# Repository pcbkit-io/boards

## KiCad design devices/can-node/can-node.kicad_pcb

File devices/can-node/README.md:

# can-node — an STM32G431 sensor node on a robot's CAN bus

A node for a robot or a machine: four 0–5 V pressure sensors and a 6-axis IMU, sent at 100 Hz as CAN
frames at 500 kbit/s. The bus and the robot's 12 V come in on one JST GH connector; the board
protects itself (reverse polarity, transients) and makes its own 3.3 V. A jumper puts the 120 Ω
terminator on the bus for the two nodes at its ends. Firmware is ST's HAL, flashed over SWD.

| | |
|---|---|
| Processor | STM32G431CBU6 (UFQFPN-48): Arm Cortex-M4F at 170 MHz (8 MHz crystal, PLL, boost mode), FDCAN1 |
| CAN | SN65HVD230 transceiver on PA12 (TX) / PA11 (RX), 500 kbit/s; SD24C TVS on CANH and CANL; 120 Ω terminator through jumper J2 |
| Inputs | J5 (2 × 4, 2.54 mm): four 0–5 V inputs, each with its ground, through an 11 k / 20 k divider and a 1 kHz filter into ADC1 IN1–IN4 (PA0–PA3), sampled by TIM6 at 100 Hz through DMA |
| IMU | ICM-42688-P at 0x68 on I2C1 (PA15 SCL, PB7 SDA) at 400 kHz, ±4 g and ±1000 °/s |
| Power | J1 (JST GH 4-pin: 12 V, CANH, CANL, GND) → AO3401A reverse-polarity P-FET → SMBJ18A TVS → TPS54331 buck → 3.3 V |
| Debug | J4: SWD (3.3 V, SWDIO, SWCLK, NRST, GND) for an ST-LINK; J3: the console (USART1 TX, RX, GND at 115200 baud) for a 3.3 V USB-serial cable; D1: status LED on PB0 |
| Board | 60 × 40 mm, 2 layers, two M3 holes |

Frames it sends (little-endian 16-bit values):

| ID | Data |
|---|---|
| 0x100 | the four inputs in mV at the connector (0–5000) |
| 0x101 | acceleration X, Y, Z in mg, the IMU's temperature in 0.01 °C |
| 0x102 | rotation X, Y, Z in 0.1 °/s |

A frame **0x200** with one byte sets the LED: 0 off, 1 on, 2 blinking.

<!-- STATUS -->
**Board status** (measured on the dev host with PCBKit's CLI): `pcbkit check`: complete — 0 errors, 0 warnings, 0 unrouted nets. 68 components, 37 nets, 494 track segments, 53 vias.
`analysis.run { lens: "ready" }`: nothing to fix, 11 to consider (below).
`pcbkit export --format fab` succeeds without `--force`: every assembled line of the BOM has an LCSC code (JLCPCB assembly).
<!-- /STATUS -->

What the readiness check asks to consider, and why it is fine here:

| Finding | Why |
|---|---|
| J2, J3, J4 are not on an edge | the terminator jumper, the console and the SWD header: set once or used on the bench, no cable stays |
| V3 comes in through J4 unprotected | the SWD header's 3.3 V is the programmer's reference, not a supply |
| D1 runs at 0.3 mA | a status LED; 1 kΩ keeps it from lighting the robot's inside |
| No test points | the console and SWD reach every signal that matters |
| U4 needs an operating load / thermal parameters / family estimates | the analysis' own caveats: the node draws about 120 mA |

## Run it in the browser

Open https://app.pcbkit.io/github/pcbkit-io/boards/tree/main/devices/can-node, open the Laboratory and
press **Build & run**: the page builds `firmware/` with ST's HAL for the STM32G431 and runs it on a
model of the chip. `sim/robot.js` is the robot around it: the gripper's two cylinders filling and
venting (supply pressure, cycle time, a leak on cylinder B, a bump of the robot are controls),
driving the four inputs and the IMU. What you see:

- **CAN_BUS1** — the bus beyond the connector as a USB-CAN adapter: every frame as an SLCAN line
  (`t1008…`); send `t2001` + `02` + CR to make the LED blink.
- **J3** — the console: `can-node 170000000 Hz`, `imu ICM-42688-P`, the inputs once a second.

The model refuses what silicon would not do (a peripheral with its clock off, a PLL outside its
limits) and says so; it does not model the bus's analog waveform or arbitration with other nodes.

## Order, flash, use

1. Order with assembly (JLCPCB: `pcbkit export --format fab`, or `fab.order` in the app).
2. Flash over SWD with an ST-LINK on J4: `pcbkit export --format firmware` gives `U1.bin` and
   `U1.hex`; `st-flash write U1.bin 0x08000000` or STM32CubeProgrammer.
3. Wire J1 to the robot's bus (12 V, CANH, CANL, GND); fit J2's shunt on the two end nodes only.

Licence: CC0 1.0.

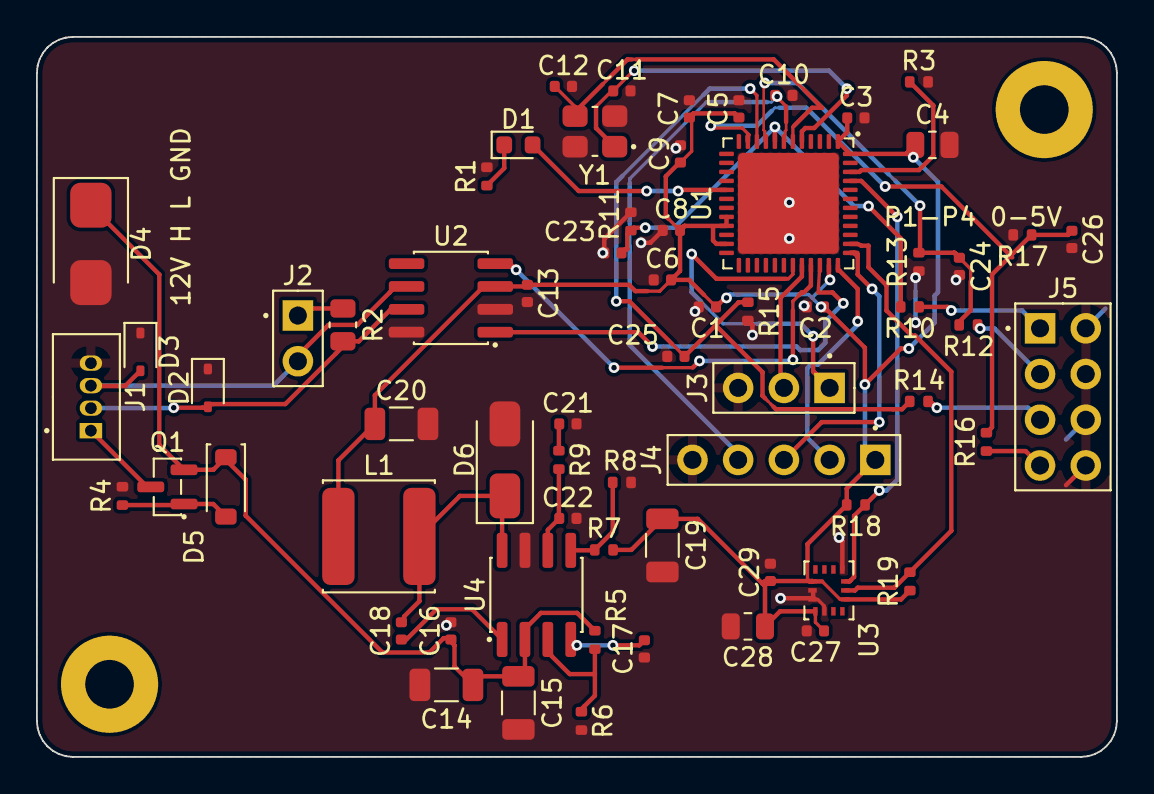
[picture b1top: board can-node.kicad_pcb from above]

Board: 2 copper layers, 60.0 x 40.0 mm, 68 parts (0 on the bottom side), 37 nets.

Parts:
C1, C2, C3, C5, C8, C10, C13, C18, C27: 100nF; C_0402_1005Metric
C4: 4.7uF; C_0805_2012Metric
C6, C16, C17, C29: 10nF; C_0402_1005Metric
C7, C9: 1uF; C_0402_1005Metric
C11, C12: 15pF; C_0402_1005Metric
C14, C15: 4.7uF; C_1206_3216Metric
C19, C20: 47uF; C_1206_3216Metric
C21: 1nF; C_0402_1005Metric
C22: 47pF; C_0402_1005Metric
C23, C24, C25, C26: 22nF; C_0402_1005Metric
C28: 2.2uF; C_0805_2012Metric
D1: green; LED_0603_1608Metric
D2, D3: tvs 24V bidir; D_SOD-323
D4: tvs 18V; D_SMB
D5: zener 5.6V; D_SOD-123
D6: schottky; D_SMA
H1, H2: MountingHole_2.7mm_M2.5_Pad
J1: SM04B-GHS-TB; Conn_WireToBoard_1x04_P1.25mm_THT_Vertical
J2: PinHeader_1x02_P2.54mm_Vertical
J3: PinHeader_1x03_P2.54mm_Vertical
J4: PinHeader_1x05_P2.54mm_Vertical
J5: PinHeader_2x04_P2.54mm_Vertical
L1: 6.8uH; L_Power_6x6mm
Q1: AO3401A; SOT-23
R1: 1kohm; R_0402_1005Metric
R2: 120ohm; R_0805_2012Metric
R3, R18, R19: 10kohm; R_0402_1005Metric
R4: 100kohm; R_0402_1005Metric
R5: 332kohm; R_0402_1005Metric
R6: 68.1kohm; R_0402_1005Metric
R7: 10.2kohm; R_0402_1005Metric
R8: 3.24kohm; R_0402_1005Metric
R9: 29.4kohm; R_0402_1005Metric
R10, R12, R14, R16: 11kohm; R_0402_1005Metric
R11, R13, R15, R17: 20kohm; R_0402_1005Metric
U1: STM32G431CBU6; QFN-48-1EP_7x7mm_P0.5mm_EP5.6x5.6mm
U2: SN65HVD230DR; SOIC-8_3.895x4.905mm_P1.27mm
U3: ICM-42688-P; LGA-14_2.5x3.0x0.91mm_0.5mm_pitch
U4: TPS54331D; SOIC-8_3.9x4.9mm_P1.27mm
Y1: 8MHz 10pF; Crystal_SMD_3225-4Pin

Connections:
A1: C23.1 (a), R10.2 (b), R11.1 (a), U1.8 (PA0)
A2: C24.1 (a), R12.2 (b), R13.1 (a), U1.9 (PA1)
A3: C25.1 (a), R14.1 (a), R15.1 (a), U1.10 (PA2)
A4: C26.1 (a), R16.2 (b), R17.1 (a), U1.11 (PA3)
CANH: D2.2 (A), J1.2, R2.2 (b), U2.7 (CANH)
CANL: D3.2 (A), J1.3, J2.2, U2.6 (CANL)
CAN_RX: U1.33 (PA11), U2.4 (R)
CAN_TX: U1.34 (PA12), U2.1 (D)
GND: C1.2 (b), C2.2 (b), C3.2 (b), C4.2 (b), C5.2 (b), C6.2 (b), C7.2 (b), C8.2 (b), C9.2 (b), C10.2 (b), C11.2 (b), C12.2 (b), C13.2 (b), C14.2 (b), C15.2 (b), C16.2 (b), C17.2 (b), C19.2 (b), C20.2 (b), C21.2 (b), C22.2 (b), C23.2 (b), C24.2 (b), C25.2 (b), C26.2 (b), C27.2 (b), C28.2 (b), C29.2 (b), D2.1 (K), D3.1 (K), D4.2 (A), D6.2 (A), J1.4, J3.3, J4.5, J5.2, J5.4, J5.6, J5.8, R1.2 (b), R3.2 (b), R4.2 (b), R6.2 (b), R8.2 (b), R11.2 (b), R13.2 (b), R15.2 (b), R17.2 (b), U1.49 (VSS), U2.2 (GND), U2.8 (RS), U3.1 (AP_AD0), U3.6 (GND), U3.7 (RESV7), U3.9 (INT2), U4.7 (GND), Y1.2 (GND), Y1.4 (GND)
LED: D1.2 (A), U1.17 (PB0)
LED_K: D1.1 (K), R1.1 (a)
NRST: C10.1 (a), J4.4, U1.7 (PG10)
unnamed: C17.1 (a), U4.4 (SS)
unnamed: C18.1 (a), U4.1 (BOOT)
unnamed: C18.2 (b), D6.1 (K), L1.2 (b), U4.8 (PH)
unnamed: C22.1 (a), R9.2 (b), U4.6 (COMP)
unnamed: R3.1 (a), U1.46 (PB8)
unnamed: R5.2 (b), R6.1 (a), U4.3 (EN)
unnamed: R7.2 (b), R8.1 (a), U4.5 (VSENSE)
P1: J5.1, R10.1 (a)
P2: J5.3, R12.1 (a)
P3: J5.5, R14.2 (b)
P4: J5.7, R16.1 (a)
RX: J3.2, U1.32 (PA10)
SCL: R19.1 (a), U1.38 (PA15), U3.13 (AP_SCL)
SDA: R18.1 (a), U1.45 (PB7), U3.14 (AP_SDA)
SWCLK: J4.3, U1.37 (PA14)
SWDIO: J4.2, U1.36 (PA13)
TERM: J2.1, R2.1 (a)
TX: J3.1, U1.31 (PA9)
U4Support/COMP_RC: C21.1 (a), R9.1 (a)
V3: C1.1 (a), C2.1 (a), C3.1 (a), C4.1 (a), C5.1 (a), C6.1 (a), C7.1 (a), C8.1 (a), C9.1 (a), C13.1 (a), C19.1 (a), C20.1 (a), C27.1 (a), C28.1 (a), C29.1 (a), J4.1, L1.1 (a), R7.1 (a), R18.2 (b), R19.2 (b), U1.1 (VBAT), U1.20 (VREFP), U1.21 (VDDA), U1.23 (VDD), U1.35 (VDD), U1.48 (VDD), U2.3 (VCC), U3.5 (VDDIO), U3.8 (VDD), U3.12 (AP_CS)
V12: C14.1 (a), C15.1 (a), C16.1 (a), D4.1 (K), D5.1 (K), Q1.2 (S), R5.1 (a), U4.2 (VIN)
VIN: J1.1, Q1.3 (D)
XIN: C11.1 (a), U1.5 (PF0), Y1.1 (X1)
XOUT: C12.1 (a), U1.6 (PF1), Y1.3 (X2)
reversed/gate: D5.2 (A), Q1.1 (G), R4.1 (a)

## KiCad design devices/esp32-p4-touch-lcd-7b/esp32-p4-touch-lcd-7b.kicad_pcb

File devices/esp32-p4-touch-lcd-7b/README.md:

# esp32-p4-touch-lcd-7b — Waveshare's ESP32-P4 7" touch board, running PocketJS

Waveshare's [ESP32-P4-WIFI6-Touch-LCD-7B](https://www.waveshare.com/wiki/ESP32-P4-WIFI6-Touch-LCD-7B)
as a PCBKit project: its circuit read from Waveshare's published schematic, its parts where
Waveshare's assembly drawing puts them (the connectors on the same edges, the chips in the same
places), behind the same 7" 1024 × 600 panel. In the app it runs
[PocketJS](https://github.com/pocket-nexus/pocketjs)'s ESP32-P4 host for this board (pull
request #208, MIT) with its stock Feature Cards app: one flash image, published by PCBKit as a
[release of this repository](https://github.com/pcbkit-io/boards/releases/tag/pocketjs-esp32p4-7b-5d4a16b9),
booted by Espressif's ESP32-P4 boot ROM on PCBKit's model of the chip.

| | |
|---|---|
| Processor | ESP32-P4NRW32 (two RISC-V cores at 360 MHz, 32 MB PSRAM in package), GD25Q256 32 MB flash, 40 MHz and 32.768 kHz crystals, a CR1220 for its clock |
| Screen | 7" 1024 × 600 IPS, EK79007 over 2-lane MIPI-DSI (P2, 30 pins), GT911 touch on I2C (J3, 6 pins, GPIO7/8, INT GPIO23); AVDD 9.6 V from an AP3012, VGH and VGL from charge pumps, the backlight from an AP3032 dimmed by GPIO32 |
| Sound | ES8311 codec, NS4150B 3 W amplifier (GPIO53) to the speaker (H7); ES7210 four-channel ADC with two ZTS6117 microphones and the speaker's own signal for echo cancelling; I2S on GPIO9–13 |
| Radio | ESP32-C6-MINI-1 on the P4's second SD/MMC slot (GPIO14–19), its antenna at the top edge |
| Storage | microSD on SD/MMC slot 0 (GPIO39–44), its supply switched by GPIO45 |
| Camera | 15-pin 1 mm MIPI-CSI connector (J2), Raspberry Pi's pinout |
| Ports | RS-485 (SP3485, automatic direction), CAN (TJA1051T/3), I2C through an NDC7002N level shifter, the console's UART, two 12-pin headers of GPIOs (PH2.0) |
| USB | USB-C console (CH343P, automatic boot), USB-C to the P4's full-speed USB, USB-A host (1 A switch) |
| Power | the two USB-C ORed by ideal diodes, a Li-ion cell (IP5306 charger and boost), a slide switch, SY8089 bucks to 3.3 V and to the P4's 1.2 V |
| Board | 165.5 × 98 mm, 6 layers (JLCPCB JLC06161H-3313), four M2.5 holes |

Parts Waveshare uses that JLCPCB did not stock (2026-10-25), each replaced by one doing the same
job: the MP1658 and MP1605 bucks by SY8089s, the DIO7003 load switch by an SY6280, the ETA6098
charger and SCT12A0 boost by an IP5306, the EMH4 dual transistor by two MMBT3904s, the THVD1406 by
an SP3485. The RS-485 gas discharge tube and the 120 Ω termination jumpers are left out.

<!-- STATUS -->
**Board status** (measured on the dev host with PCBKit's CLI): `pcbkit check`: complete — 0 errors,
47 warnings (the DSI, CSI and USB pairs' coupling and skew: the router lays each pair as two
tracks; 26 tracks narrowed to 0.09 mm between the P4's pins; one 3.3 V track's current), 0
unrouted nets. 293 components, 206 nets, 3993 track segments, 852 vias.
`analysis.run { lens: "ready" }`: 17 to fix — the FPC connectors (P2, J3, J2) inside the board, as
the panel's tails and the camera's ribbon reach them from behind; decoupling 3–6 mm from some P4
pins (its 0402s on the back) and 10–14 mm from the C6 and the IP5306; the analysis's estimate of
ground's heating (it gives each ground stub to the plane the board's whole current).
Every assembled line has its LCSC code (110, chosen by stock at JLCPCB, 2026-10-25); `pcbkit export
--format fab` succeeds without `--force`. **JLCPCB has no ESP32-P4 in stock**: send it as a
consigned part.
<!-- /STATUS -->

## Run it in the browser

Open the board and press **Run**: the page fetches the PocketJS image (checked against the
SHA-256 this design declares) and Espressif's ROM, and runs them. Feature Cards comes up in
about seven seconds; tap a card on the screen in 3D and it opens its details. The same release has
PocketJS's Music ("Now Playing") and Chrome apps for this host: put one of their URLs, SHA-256s
and sizes into the processor's `image` to run it instead. The console (H8) shows PocketJS's
log.

What does not run here, and says so:

- **No radio.** The ESP32-C6 is on the board but held in reset: its firmware (ESP-Hosted) does
  not run, so there is no Wi-Fi or Bluetooth. Nothing pretends to be a network.
- **CAN.** PCBKit's ESP32-P4 model has no TWAI controller yet: the TJA1051 stays unconnected
  (the laboratory lists it among its limitations).
- The ES7210 (the microphones), the camera and the RS-485 transceiver have no models yet.

## Order, flash

1. Order with assembly (`pcbkit export --format fab`); the panel plugs into P2 and J3. JLCPCB has
   no ESP32-P4 in stock: send it as a consigned part.
2. Flash over the console's USB-C: `esptool.py --chip esp32p4 write_flash 0
   pocketjs-esp32p4-waveshare-7b-cards-factory.bin` (the CH343P's DTR and RTS put the P4 into
   its boot loader).

Licence: the board CC0 1.0; Waveshare's schematic is its own, read for the circuit (no files of
it here); PocketJS MIT, fetched from the release and never copied into the project.

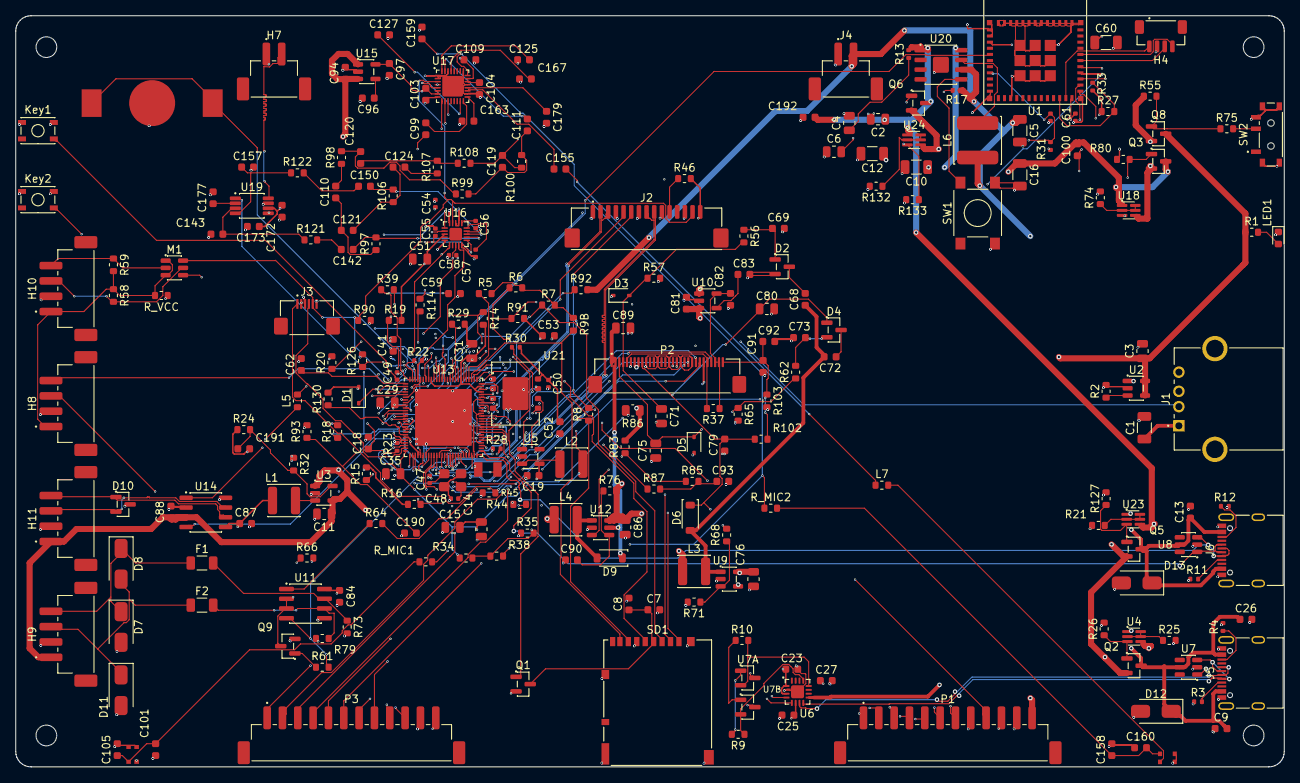
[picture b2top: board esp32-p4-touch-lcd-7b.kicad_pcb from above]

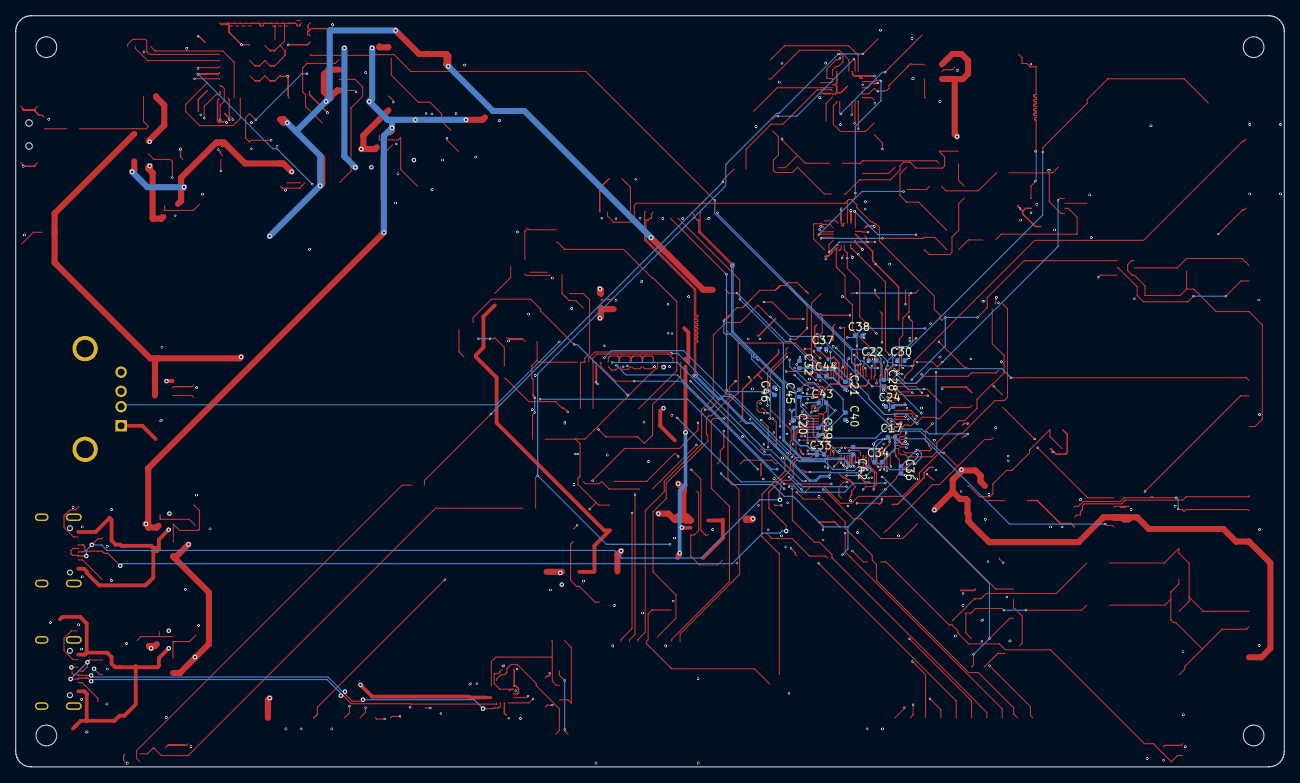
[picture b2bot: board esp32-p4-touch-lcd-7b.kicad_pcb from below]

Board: 6 copper layers, 165.5 x 98.0 mm, 293 parts (21 on the bottom side), 203 nets.

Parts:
BAT1: KH-CR1220-2; BatteryHolder_CR1220_SMD
C1: 100uF; C_1206_3216Metric
C2, C3, C4, C6, C29, C31, C35, C51, C71, C75, C76, C80, C86: 10uF; C_0805_2012Metric
C5, C10, C12, C16, C60: 22uF; C_1206_3216Metric
C7, C18, C19, C52, C92, C94, C97, C172: 10uF; C_0603_1608Metric
C8, C26, C27, C53, C68, C72, C79, C84, C87, C88, C91, C93, C103, C104, C105, C142, C150, C160, C173, C190: 100nF; C_0603_1608Metric
C9, C13, C23, C25, C41, C69, C73, C81, C82, C90, C99, C100, C109, C127, C155, C159, C163, C167, C177, C179, C192: 1uF; C_0603_1608Metric
C11, C14, C15: 22uF; C_0805_2012Metric
C17, C20, C21, C22, C24, C28, C30, C32, C33, C34, C36, C37, C38, C39, C40, C42, C50, C54, C61: 100nF; C_0402_1005Metric
C43, C44, C45, C46, C49, C55, C56, C57, C58, C63: 1uF; C_0402_1005Metric
C47, C48: 15pF; C_0402_1005Metric
C59, C62, C143, C157, C191: 22pF; C_0603_1608Metric
C83, C96: 22nF; C_0603_1608Metric
C89: 1uF; C_0805_2012Metric
C101, C158: 2.2uF; C_0603_1608Metric
C110, C124: 470nF; C_0603_1608Metric
C111, C125: 220nF; C_0603_1608Metric
C119: 100pF; C_0603_1608Metric
C120: 2.2nF; C_0603_1608Metric
C121: 10nF; C_0603_1608Metric
D1: schottky; D_SOD-323
D2, D4: BAT54S-7-F; SOT-23
D3: zener 7.5V; D_SOD-323
D5: zener 18V; D_SOD-323
D6, D9: schottky; D_SOD-123
D7, D8, D11: tvs 12V bidir; D_SMA
D10: SM24CANB-02HTG; SOT-23
D12, D13: tvs 5V; D_SMA
F1, F2: PTC 200mA; Fuse_1206_3216Metric
H4: SH1.0-4P SMD vertical; Conn_WireToBoard_1x04_P1.00mm_SMD_Vertical
H7: PH2.0-2P SMD vertical; Conn_WireToBoard_1x02_P2.00mm_SMD_Vertical
H8, H9, H10, H11: PH2.0-4P SMD vertical; Conn_WireToBoard_1x04_P2.00mm_SMD_Vertical
J1: USB-A 90deg; USB_A_Receptacle_THT_Horizontal
J2: FPC 1.0mm 15P flip-lock bottom contact; Conn_FFC-FPC_1x15_P1.00mm_Horizontal
J3: FPC 0.5mm 6P flip-lock top contact; Conn_FFC-FPC_1x06_P0.50mm_Horizontal
J4: PH2.0-2P SMD vertical; Conn_WireToBoard_1x02_P2.00mm_SMD_Vertical
J5, J6: USB4105-GF-A; USB_C_Receptacle_USB2.0_16P
Key1, Key2: PTS810SJM250SMTR LFS; SW_Tactile_SPST_4.2x3.2mm_SMD
L1, L2: 2.2uH; L_Power_4x4mm
L3, L4: 10uH; L_Power_4x4mm
L5, L7: 0uohm; R_0603_1608Metric
L6: 1uH; L_Power_6x6mm
LCD1: touch-display; Waveshare-7inch-1024x600-DSI
LED1: red; LED_0603_1608Metric
LSK1, LSK2, LSK3, LSK4: MountingHole_2.7mm_M2.5
M1: NDC7002N; SOT-23-6
MIC1, MIC2: ZTS6117; MEMS_Mic_ZTS6117_2.75x1.85mm
P1, P3: PH2.0-12P SMD vertical; Conn_WireToBoard_1x12_P2.00mm_SMD_Vertical
P2: FPC 0.5mm 30P flip-lock bottom contact; Conn_FFC-FPC_1x30_P0.50mm_Horizontal
Q1, Q2, Q3, Q5, Q6, Q8: AO3401A; SOT-23
Q9: MMBT3904-7-F; SOT-23
R1: 7.5kohm; R_0603_1608Metric
R2: 6.8kohm; R_0603_1608Metric
R3, R4, R11, R12: 5.1kohm; R_0402_1005Metric
R5, R6, R7, R8, R9, R9B, R10, R14, R21, R25, R27, R29, R37, R45, R46, R73, R74, R75, R79, R87, R98, R107, R126, R132: 10kohm; R_0603_1608Metric
R13, R17: 2ohm; R_0402_1005Metric
R15, R16, R18, R19, R20, R26, R57, R65, R80, R127, R130, R133: 51kohm; R_0603_1608Metric
R22, R30, R31, R33: 10kohm; R_0402_1005Metric
R23, R28: 2kohm; R_0402_1005Metric
R24: 453kohm; R_0603_1608Metric
R32, R76, R93: 100kohm; R_0603_1608Metric
R34, R35: 499kohm; R_0603_1608Metric
R38: 0uohm; R_0603_1608Metric
R39: 10Mohm; R_0603_1608Metric
R44, R58, R59, R61, R64, R66: 4.7kohm; R_0603_1608Metric
R55: 110kohm; R_0603_1608Metric
R56, R62: 220ohm; R_0603_1608Metric
R68: 22kohm; R_0603_1608Metric
R71: 3.3kohm; R_0603_1608Metric
R83: 5.1kohm; R_0603_1608Metric
R85: 68kohm; R_0603_1608Metric
R86: 1.3ohm; R_0805_2012Metric
R90, R91, R97, R106: 2.2kohm; R_0603_1608Metric
R92: 200kohm; R_0603_1608Metric
R99, R108: 20kohm; R_0603_1608Metric
R100: 4.3kohm; R_0603_1608Metric
R102: 2kohm; R_0603_1608Metric
R103: 1kohm; R_0603_1608Metric
R114: 51ohm; R_0603_1608Metric
R121, R122: 150kohm; R_0603_1608Metric
R_MIC1, R_MIC2: 0uohm; R_0603_1608Metric
R_VCC: 0uohm; R_0603_1608Metric
SD1: DM3AT-SF-PEJM5; Hirose_DM3AT_microSD_socket_push-push
SW1: PTS645SM43SMTR92 LFS; SW_Tactile_SPST_6x6mm_SMD
SW2: MSK12C02; SW_Slide_SPDT_Shouhan_MSK12C02
U1: ESP32-C6-MINI-1-N4; ESP32-C6-MINI-1_module_13.2x16.6mm_LGA_53_pads
U2: SY6280AAC; SOT-23-5
U3, U5: SY8089AAAC; SOT-23-5
U4, U18, U23, U24: MMDT3906DW; SOT-363
U6: CH343P; QFN-16-1EP_3x3mm_P0.5mm_EP1.7x1.7mm
U7, U8: USBLC6-2SC6; SOT-23-6
U7A, U7B: MMBT3904-7-F; SOT-23
U9: AP3012KTR-E1; SOT-23-5
U10: RT9193-18GB; SOT-23-5
U11: SP3485EN-L/TR; SOIC-8_3.9x4.9mm_P1.27mm
U12: AP3032KTR-G1; SOT-23-6
U13: ESP32-P4NRW32; QFN-104_10x10mm_0.35mm_pitch_7.5mm_exposed_pad
U14: TJA1051T/3/1J; SOIC-8_3.9x4.9mm_P1.27mm
U15: RT9193-33GB; SOT-23-5
U16: ES8311; QFN-20-1EP_3x3mm_P0.4mm_EP1.65x1.65mm
U17: ES7210; QFN-32-1EP_4x4mm_P0.4mm_EP2.7x2.7mm
U19: NS4150B; MSOP-8_3x3mm_P0.65mm
U20: IP5306; SOIC-8-1EP_3.9x4.9mm_P1.27mm_EP2.09x2.09mm
U21: GD25Q256EYIGR; DFN-8-1EP_6x8mm_P1.27mm_EP3.4x4.3mm
Y1: 40MHz 10pF; Crystal_SMD_3225-4Pin
Y3: Q13FC13500004; Crystal_SMD_3215-2Pin_3.2x1.5mm

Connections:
A3V3: C55.1 (a), C97.1 (a), C103.1 (a), C104.1 (a), C109.1 (a), U15.5 (VOUT), U16.11 (AVDD), U17.6 (VDDP), U17.7 (VDDD), U17.22 (VDDA), U17.23 (VDDM)
A3V3_BP: C96.1 (a), U15.4 (BP)
ADC_MIC3_N: C125.2 (b), U17.32 (MIC3N)
ADC_MIC3_P: C111.2 (b), U17.31 (MIC3P)
ADC_MICBIAS12: C159.1 (a), R_MIC1.1 (a), R_MIC2.1 (a), U17.24 (MICBIAS12)
AEC_N1: C121.2 (b), C124.1 (a), R106.2 (b)
AEC_N2: C124.2 (b), R107.1 (a)
AEC_N3: C120.2 (b), R107.2 (b), R108.1 (a)
AEC_N4: C119.2 (b), C125.1 (a), R100.2 (b), R108.2 (b)
AEC_P1: C110.1 (a), C121.1 (a), R97.2 (b)
AEC_P2: C110.2 (b), R98.1 (a)
AEC_P3: C120.1 (a), R98.2 (b), R99.1 (a)
AEC_P4: C111.1 (a), C119.1 (a), R99.2 (b), R100.1 (a)
AVDD: C79.1 (a), C80.1 (a), D4.1 (A1), D6.1 (K), P2.9, R68.1 (a), R102.2 (b)
AVDD_FB: R68.2 (b), R71.1 (a), U9.3 (FB)
BAT: C5.1 (a), J4.2, L6.1 (a), P1.12, R17.1 (a), R92.1 (a), U20.6 (BAT)
BAT_SENSE: C190.1 (a), R92.2 (b), R93.1 (a), U13.22 (GPIO20)
BL_CTRL: R87.1 (a), U13.63 (GPIO32)
BL_DIM: C93.1 (a), R85.2 (b), R87.2 (b)
BL_EN: C90.1 (a), R76.1 (a), U12.4 (EN)
BL_FB: R83.2 (b), R85.1 (a), U12.3 (FB)
BL_SW: D9.2 (A), L4.1 (a), U12.1 (SW)
BOOST_5V: C10.1 (a), C12.1 (a), C16.1 (a), C100.1 (a), Q3.3 (D), U18.1 (E2), U20.8 (VOUT)
BOOT: Key2.1 (a), R44.1 (a), U7B.3 (C), U13.66 (GPIO35)
C6_CHIP_PU: C63.1 (a), R31.1 (a), U1.8 (EN), U13.98 (GPIO54)
C6_CLK: R20.1 (a), U1.25 (IO19), U13.19 (GPIO18)
C6_CMD: R130.1 (a), U1.24 (IO18), U13.20 (GPIO19)
C6_D0: R19.1 (a), U1.26 (IO20), U13.15 (GPIO14)
C6_D1: R18.1 (a), U1.27 (IO21), U13.16 (GPIO15)
C6_D2: R16.1 (a), U1.28 (IO22), U13.17 (GPIO16)
C6_D3: R15.1 (a), U1.29 (IO23), U13.18 (GPIO17)
C6_IO2: U1.5 (IO2), U13.6 (GPIO6)
C6_IO8: R27.1 (a), R33.1 (a), U1.22 (IO8)
C6_IO9: H4.1, U1.23 (IO9)
C6_U0RXD: H4.3, U1.30 (RXD0)
C6_U0TXD: H4.4, U1.31 (TXD0)
CANH: D10.2 (H), H11.3, U14.7 (CANH)
CANL: D10.1 (L), H11.4, U14.6 (CANL)
CANRX: U13.23 (GPIO21), U14.4 (RXD)
CANTX: U13.24 (GPIO22), U14.1 (TXD)
CORE_5V: C3.1 (a), C11.1 (a), C76.1 (a), C81.1 (a), C86.1 (a), C88.1 (a), C94.1 (a), H9.1, H11.1, L3.1 (a), L4.2 (b), Q8.3 (D), R1.1 (a), R76.2 (b), U2.4 (EN), U2.5 (IN), U3.1 (EN), U3.4 (IN), U9.4 (SHDN), U9.5 (VIN), U10.1 (VIN), U10.3 (EN), U12.6 (VIN), U14.3 (VCC), U15.1 (VIN), U15.3 (EN)
CSI_CLK_N: J2.8, U13.45 (CSI_CLKN)
CSI_CLK_P: J2.9, U13.44 (CSI_CLKP)
CSI_D0_N: J2.2, U13.42 (CSI_DATAN0)
CSI_D0_P: J2.3, U13.43 (CSI_DATAP0)
CSI_D1_N: J2.5, U13.46 (CSI_DATAN1)
CSI_D1_P: J2.6, U13.47 (CSI_DATAP1)
CSI_IO0: J2.11, R46.1 (a)
DSI_CLK_N: P2.18, U13.37 (DSI_CLKN)
DSI_CLK_P: P2.17, U13.38 (DSI_CLKP)
DSI_D0_N: P2.24, U13.40 (DSI_DATAN0)
DSI_D0_P: P2.23, U13.39 (DSI_DATAP0)
DSI_D1_N: P2.21, U13.36 (DSI_DATAN1)
DSI_D1_P: P2.20, U13.35 (DSI_DATAP1)
DTR: R10.2 (b), U6.12 (DTR#), U7A.2 (E)
D_SCL: H10.4, M1.2 (S2), R59.1 (a)
D_SDA: H10.3, M1.5 (S1), R58.2 (b)
EN_DCDC: U5.1 (EN), U13.79 (EN_DCDC)
ES7210_REFP12: C163.1 (a), U17.17 (REFP12)
ES7210_REFP34: C167.1 (a), U17.29 (REFP34)
ES7210_SDOUT: R114.1 (a), U17.11 (SDOUT1)
ESP_3V3: C14.1 (a), C15.1 (a), C17.1 (a), C19.1 (a), C20.1 (a), C21.1 (a), C22.1 (a), C23.1 (a), C24.1 (a), C25.1 (a), C27.1 (a), C29.1 (a), C30.1 (a), C31.1 (a), C32.1 (a), C33.1 (a), C34.1 (a), C50.1 (a), C51.1 (a), C52.1 (a), C53.1 (a), C54.1 (a), C60.1 (a), C61.1 (a), C84.1 (a), C87.1 (a), C172.1 (a), C173.1 (a), C191.1 (a), D1.2 (A), J2.15, J3.2, L1.2 (b), P1.10, P3.12, Q1.2 (S), R14.2 (b), R15.2 (b), R16.2 (b), R18.2 (b), R19.2 (b), R20.2 (b), R22.2 (b), R24.1 (a), R27.2 (b), R30.2 (b), R31.2 (b), R33.2 (b), R44.2 (b), R46.2 (b), R66.2 (b), R79.2 (b), R90.2 (b), R91.2 (b), R130.2 (b), R_VCC.1 (a), U1.3 (P3V3), U5.4 (IN), U6.1 (VIO), U6.3 (VDD5), U6.6 (V3), U11.8 (VCC), U13.9 (VDD_LP), U13.21 (VDD_IO_0), U13.30 (VDD_FLASHIO), U13.51 (VDD_USBPHY), U13.62 (VDD_IO_4), U13.75 (VDD_LDO), U13.77 (VDD_DCDCC), U13.85 (VDD_IO_5), U13.96 (VDD_IO_6), U13.101 (VDD_ANA), U14.5 (VIO), U16.3 (PVDD), U16.4 (DVDD), U19.6 (VDD), U21.8 (VCC)
ESP_EN: C49.1 (a), Key1.1 (a), R22.1 (a), U7A.3 (C), U13.103 (CHIP_PU)
ESP_I2C_SCL: J2.13, J3.6, M1.4 (D2), R91.1 (a), U13.8 (GPIO8), U16.1 (CCLK), U17.4 (CCLK)
ESP_I2C_SDA: J2.14, J3.5, M1.6 (D1), R90.1 (a), U13.7 (GPIO7), U16.19 (CDATA), U17.3 (CDATA)
ESP_LDO_VO4: C46.1 (a), P1.9, R5.2 (b), R6.2 (b), R7.2 (b), R8.1 (a), R9B.1 (a), U13.74 (VDDO_4)
ESP_VBAT: BAT1.1 (+), C28.1 (a), C41.1 (a), D1.1 (K), U13.102 (VDD_BAT)
ESP_VDD_HP: C18.1 (a), C35.1 (a), C36.1 (a), C37.1 (a), C38.1 (a), L2.1 (a), R34.2 (b), U13.26 (VDD_HP_0), U13.76 (VDD_HP_2), U13.91 (VDD_HP_3)
FB_DCDC: R38.1 (a), U13.78 (FB_DCDC)
GND: BAT1.2 (-), C1.2 (b), C2.2 (b), C3.2 (b), C4.2 (b), C5.2 (b), C6.2 (b), C7.2 (b), C8.2 (b), C9.2 (b), C10.2 (b), C11.2 (b), C12.2 (b), C13.2 (b), C14.2 (b), C15.2 (b), C16.2 (b), C17.2 (b), C18.2 (b), C19.2 (b), C20.2 (b), C21.2 (b), C22.2 (b), C23.2 (b), C24.2 (b), C25.2 (b), C26.2 (b), C27.2 (b), C28.2 (b), C29.2 (b), C30.2 (b), C31.2 (b), C32.2 (b), C33.2 (b), C34.2 (b), C35.2 (b), C36.2 (b), C37.2 (b), C38.2 (b), C39.2 (b), C40.2 (b), C41.2 (b), C42.2 (b), C43.2 (b), C44.2 (b), C45.2 (b), C46.2 (b), C47.2 (b), C48.2 (b), C49.2 (b), C50.2 (b), C51.2 (b), C52.2 (b), C53.2 (b), C54.2 (b), C55.2 (b), C56.2 (b), C57.2 (b), C58.2 (b), C59.2 (b), C60.2 (b), C61.2 (b), C62.2 (b), C63.2 (b), C69.2 (b), C71.2 (b), C73.2 (b), C75.2 (b), C76.2 (b), C79.2 (b), C80.2 (b), C81.2 (b), C82.2 (b), C83.2 (b), C84.2 (b), C86.2 (b), C87.2 (b), C88.2 (b), C89.2 (b), C90.2 (b), C91.2 (b), C92.2 (b), C93.2 (b), C94.2 (b), C96.2 (b), C97.2 (b), C100.2 (b), C101.2 (b), C103.2 (b), C104.2 (b), C105.2 (b), C109.2 (b), C127.2 (b), C143.2 (b), C157.2 (b), C158.2 (b), C159.2 (b), C160.2 (b), C163.2 (b), C167.2 (b), C172.2 (b), C173.2 (b), C177.2 (b), C179.2 (b), C190.2 (b), C192.2 (b), D2.2 (K2), D3.1 (K), D5.2 (A), D7.2 (A), D10.3 (GND), D11.2 (A), D12.2 (A), D13.2 (A), H4.2, H8.2, H9.2, H10.2, H11.2, J1.4 (GND), J2.1, J2.4, J2.7, J2.10, J3.3, J4.1, J5.A1 (GND), J5.A12, J5.B1 (GND), J5.B12, J5.S1 (SHIELD), J6.A1 (GND), J6.A12, J6.B1 (GND), J6.B12, J6.S1 (SHIELD), Key1.2 (b), Key2.2 (b), LED1.1 (K), MIC1.2 (GND), MIC1.3 (GND), MIC2.2 (GND), MIC2.3 (GND), P1.8, P1.11, P2.6, P2.10, P2.13, P2.16, P2.19, P2.22, P2.25, P3.11, Q9.2 (E), R2.2 (b), R3.2 (b), R4.2 (b), R11.2 (b), R12.2 (b), R21.2 (b), R23.2 (b), R25.2 (b), R26.2 (b), R28.2 (b), R29.2 (b), R32.2 (b), R35.2 (b), R45.2 (b), R57.2 (b), R65.2 (b), R71.2 (b), R73.2 (b), R74.2 (b), R80.2 (b), R86.2 (b), R93.2 (b), R103.2 (b), R126.2 (b), R127.2 (b), R132.2 (b), R133.2 (b), SD1.6 (VSS), SD1.SH, SW1.2 (b), SW2.3 (B), SW2.4 (SHELL), U1.1 (GND), U1.2 (GND), U1.11 (GND), U1.14 (GND), U1.36 (GND), U1.37 (GND), U1.38 (GND), U1.39 (GND), U1.40 (GND), U1.41 (GND), U1.42 (GND), U1.43 (GND), U1.44 (GND), U1.45 (GND), U1.46 (GND), U1.47 (GND), U1.48 (GND), U1.49 (GND), U1.50 (GND), U1.51 (GND), U1.52 (GND), U1.53 (GND), U2.2 (GND), U3.2 (GND), U5.2 (GND), U6.2 (GND), U6.17 (GND), U7.2 (GND), U8.2 (GND), U9.2 (GND), U10.2 (GND), U11.5 (GND), U12.2 (GND), U13.105 (GND), U14.2 (GND), U14.8 (S), U15.2 (GND), U16.5 (DGND), U16.10 (AGND), U16.17 (MIC1N), U16.18 (MIC1P), U16.20 (CE), U17.1 (AD0), U17.2 (AD1), U17.8 (GNDD), U17.18 (REFQ12), U17.21 (GNDA), U17.25 (REFQM), U17.30 (REFQ34), U17.33 (E_GND), U19.7 (GND), U20.9 (GND), U21.4 (GND), U21.9 (GND), Y1.2 (GND), Y1.4 (GND)
GPIO2: P3.10, U13.2 (GPIO2)
GPIO3: P3.9, U13.3 (GPIO3)
GPIO4: P3.8, U13.4 (GPIO4)
GPIO5: P3.7, U13.5 (GPIO5)
GPIO28: P3.6, U13.57 (GPIO28)
GPIO29: P3.5, U13.58 (GPIO29)
GPIO30: P3.4, U13.60 (GPIO30)
GPIO31: P3.3, U13.61 (GPIO31)
GPIO34: P3.2, U13.65 (GPIO34)
GPIO36: P3.1, R14.1 (a), U13.68 (GPIO36)
GPIO46: P1.7, U13.88 (GPIO46)
GPIO47: P1.6, U13.89 (GPIO47)
GPIO48: P1.5, U13.90 (GPIO48)
GPIO49: P1.4, U13.92 (GPIO49)
GPIO50: P1.3, U13.93 (GPIO50)
GPIO51: P1.2, U13.94 (GPIO51)
GPIO52: P1.1, U13.95 (GPIO52)
H1/power/cc1: J5.A5 (CC1), R3.1 (a)
H1/power/cc2: J5.B5 (CC2), R4.1 (a)
H2/power/cc1: J6.A5 (CC1), R11.1 (a)
H2/power/cc2: J6.B5 (CC2), R12.1 (a)
HP_FB: R34.1 (a), R35.1 (a), R38.2 (b), U5.5 (FB)
I2S_ASDOUT: R114.2 (b), U13.12 (GPIO11)
I2S_DSDIN: U13.10 (GPIO9), U16.9 (DSDIN)
I2S_LRCK: U13.11 (GPIO10), U16.8 (LRCK), U17.10 (LRCK)
I2S_MCLK: U13.14 (GPIO13), U16.2 (MCLK), U17.5 (MCLK)
I2S_SCLK: U13.13 (GPIO12), U16.6 (SCLK), U17.9 (SCLK)
INT_TP: J3.4, U13.25 (GPIO23)
ISET: R2.1 (a), U2.3 (ISET)
KEY: R75.2 (b), SW2.2 (COM)
LCD_STBY: P2.5, P2.26, R37.2 (b)
LCD_SW: C68.1 (a), C72.2 (b), D6.2 (A), L3.2 (b), U9.1 (SW)
LED1_A: LED1.2 (A), R1.2 (b)
LEDN: P2.7, P2.8, R83.1 (a), R86.1 (a)
LEDP: C89.1 (a), D9.1 (K), P2.1, P2.2, U12.5 (OV)
MIC1_BIAS: C101.1 (a), C105.1 (a), MIC1.4 (VDD), R_MIC1.2 (b)
MIC1_DAT: L5.1 (a), MIC1.1 (OUT)
MIC1_N: C127.1 (a), U17.15 (MIC1N)
MIC1_OUT: C99.1 (a), L5.2 (b)
MIC1_P: C99.2 (b), U17.16 (MIC1P)
MIC2_BIAS: C158.1 (a), C160.1 (a), MIC2.4 (VDD), R_MIC2.2 (b)
MIC2_DAT: L7.1 (a), MIC2.1 (OUT)
MIC2_N: C179.1 (a), U17.20 (MIC2N)
MIC2_OUT: C155.1 (a), L7.2 (b)
MIC2_P: C155.2 (b), U17.19 (MIC2P)
unnamed: C39.1 (a), C40.1 (a), C44.1 (a), U13.59 (VDD_PSRAM_0), U13.67 (VDD_PSRAM_1), U13.72 (VDDO_PSRAM)
unnamed: C42.1 (a), C45.1 (a), U13.41 (VDD_MIPI_DPHY), U13.73 (VDDO_3)
unnamed: C43.1 (a), U13.71 (VDDO_FLASH)
unnamed: C47.1 (a), U13.100 (XTAL_P), Y1.1 (X1)
unnamed: C48.1 (a), U13.99 (XTAL_N), Y1.3 (X2)
unnamed: C56.1 (a), U16.16 (VMID)
unnamed: C57.1 (a), U16.15 (ADCVREF)
unnamed: C58.1 (a), U16.14 (DACVREF)
unnamed: L1.1 (a), U3.3 (LX)
unnamed: L2.2 (b), U5.3 (LX)
unnamed: L6.2 (b), U20.7 (SW)
unnamed: R23.1 (a), U13.34 (DSI_REXT)
unnamed: R28.1 (a), U13.48 (CSI_REXT)
unnamed: R30.1 (a), U13.27 (FLASH_CS), U21.1 (nCS)
unnamed: SW1.1 (a), U20.5 (KEY)
unnamed: U13.28 (FLASH_Q), U21.2 (DO)
unnamed: U13.29 (FLASH_WP), U21.3 (nWP)
unnamed: U13.31 (FLASH_HOLD), U21.7 (nHOLD)
unnamed: U13.32 (FLASH_CK), U21.6 (CLK)
unnamed: U13.33 (FLASH_D), U21.5 (DI)
OUTN: C150.1 (a), R106.1 (a), U16.13 (OUTN)
OUTP: C142.1 (a), R97.1 (a), U16.12 (OUTP)
PA_BYPASS: C177.1 (a), U19.2 (BYPASS)
PA_CTRL: R126.1 (a), U13.97 (GPIO53), U19.1 (CTRL)
PA_IN1N: C150.2 (b), R122.1 (a)
PA_IN1P: C142.2 (b), R121.1 (a)
PA_INLN: C157.1 (a), R122.2 (b), U19.4 (IN-)
PA_INLP: C143.1 (a), R121.2 (b), U19.3 (IN+)
PA_OUTLN: H7.1, U19.5 (OUT-)
PA_OUTLP: H7.2, U19.8 (OUT+)
PUMP_H: C72.1 (a), D4.3 (COM)
PUMP_L: C68.2 (b), D2.3 (COM)
Q2B: R25.1 (a), U4.2 (B2), U4.5 (B1), U4.6 (C2)
Q2G: Q2.1 (G), R26.1 (a), U4.3 (C1)
Q3B: R74.1 (a), U18.2 (B2), U18.5 (B1), U18.6 (C2)
Q3G: Q3.1 (G), R80.1 (a), U18.3 (C1)
Q5B: R21.1 (a), U23.2 (B2), U23.5 (B1), U23.6 (C2)
Q5G: Q5.1 (G), R127.1 (a), U23.3 (C1)
Q6B: R132.1 (a), U24.2 (B2), U24.5 (B1), U24.6 (C2)
Q6G: Q6.1 (G), R133.1 (a), U24.3 (C1)
Q8G: Q8.1 (G), R55.2 (b), R75.1 (a)
Q9B: Q9.1 (B), R61.2 (b)
QDTRB: R9.2 (b), U7A.1 (B)
QRTSB: R10.1 (a), U7B.1 (B)
RESET_LCD: J3.1, P2.27, R45.1 (a), U13.64 (GPIO33)
RS485_A: F2.2 (b), R79.1 (a), U11.6 (A)
RS485_B: F1.2 (b), R73.1 (a), U11.7 (B)
RS485_DE: Q9.3 (C), R66.1 (a), U11.2 (RE), U11.3 (DE)
RS485_LA: D8.2 (A), D11.1 (K), F2.1 (a), H9.3
RS485_LB: D7.1 (K), D8.1 (K), F1.1 (a), H9.4
RS485_RO: R64.1 (a), U11.1 (RO)
RS485_RXD: R61.1 (a), U11.4 (DI), U13.56 (GPIO27)
RS485_TXD: R64.2 (b), U13.55 (GPIO26)
RTS: R9.1 (a), U6.13 (RTS#), U7B.2 (E)
SD1_VDD: C7.1 (a), C8.1 (a), Q1.3 (D), SD1.4 (VDD)
SD_CLK: SD1.5 (CLK), U13.84 (GPIO43)
SD_CMD: R7.1 (a), SD1.3 (CMD), U13.86 (GPIO44)
SD_D0: R8.2 (b), SD1.7 (DAT0), U13.80 (GPIO39)
SD_D1: R9B.2 (b), SD1.8 (DAT1), U13.81 (GPIO40)
SD_D2: R5.1 (a), SD1.1 (DAT2), U13.82 (GPIO41)
SD_D3: R6.1 (a), SD1.2 (CD_DAT3), U13.83 (GPIO42)
SD_PWR_EN: Q1.1 (G), R29.1 (a), U13.87 (GPIO45)
U0RXD: H8.4, U6.4 (TXD), U13.70 (GPIO38)
U0TXD: H8.3, U6.5 (RXD), U13.69 (GPIO37)
U20Support/C6_P: C4.1 (a), R13.1 (a)
U20Support/C7_P: C6.1 (a), R17.2 (b)
USB0_5V: C9.1 (a), C26.1 (a), D12.1 (K), J5.A4 (VBUS), J5.A9, J5.B4 (VBUS), J5.B9, Q2.3 (D), U4.1 (E2), U6.9 (VBUS), U7.5 (VBUS)
USB1P1_N: J6.A7 (DN), J6.B7 (DN), U8.3 (IO2), U13.52 (GPIO24)
USB1P1_P: J6.A6 (DP), J6.B6 (DP), U8.1 (IO1), U13.53 (GPIO25)
USB1_5V: C13.1 (a), D13.1 (K), J6.A4 (VBUS), J6.A9, J6.B4 (VBUS), J6.B9, Q5.3 (D), U8.5 (VBUS), U23.1 (E2)
USBD_N: J1.2 (D-), U13.49 (USB_DM)
USBD_P: J1.3 (D+), U13.50 (USB_DP)
USB_DBG_N: J5.A7 (DN), J5.B7 (DN), U6.8 (UD-), U7.3 (IO2)
USB_DBG_P: J5.A6 (DP), J5.B6 (DP), U6.7 (UD+), U7.1 (IO1)
V3_FB: C191.2 (b), R24.2 (b), R32.1 (a), U3.5 (FB)
VBUS_OUT: C1.1 (a), J1.1 (VBUS), U2.1 (OUT)
VCC: H8.1, H10.1, M1.1 (G1), M1.3 (G2), R58.1 (a), R59.2 (b), R_VCC.2 (b)
VCCP_5V: C2.1 (a), C192.1 (a), Q2.2 (S), Q5.2 (S), Q6.3 (D), R13.2 (b), U4.4 (E1), U20.1 (VIN), U23.4 (E1), U24.1 (E2)
VCC_1V8: C82.1 (a), P2.28, P2.29, R37.1 (a), U10.5 (VOUT)
VCC_1V8_BP: C83.1 (a), U10.4 (BP)
VCC_5V: Q3.2 (S), Q6.2 (S), Q8.2 (S), R55.1 (a), U18.4 (E1), U24.4 (E1)
VCOM: C91.1 (a), C92.1 (a), P2.30, R102.1 (a), R103.1 (a)
VGH: C75.1 (a), D5.1 (K), P2.3, R62.2 (b), R65.1 (a)
VGH_RAW: C73.1 (a), D4.2 (K2), R62.1 (a)
VGL: C71.1 (a), D3.2 (A), P2.4, R56.2 (b), R57.1 (a)
VGL_RAW: C69.1 (a), D2.1 (A1), R56.1 (a)
XTAL32_N: C62.1 (a), R39.2 (b), U13.1 (GPIO1), Y3.2
XTAL32_P: C59.1 (a), R39.1 (a), U13.104 (GPIO0), Y3.1
